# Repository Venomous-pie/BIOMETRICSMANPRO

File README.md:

# Biometrics Time-In/Out System

An ESP32-based biometric attendance system. A fingerprint scanner node (WROOM) communicates wirelessly via ESP-NOW to a touchscreen display node (CrowPanel), which connects to the backend over WiFi.

---

## Table of Contents

1. [Architecture Overview](#1-architecture-overview)
2. [Hardware](#2-hardware)
3. [Power Requirements](#3-power-requirements)
4. [Wiring & Pinout](#4-wiring--pinout)
5. [Arduino IDE Setup](#5-arduino-ide-setup)
6. [Configuration Reference](#6-configuration-reference)
7. [First-Time Flash Order](#7-first-time-flash-order)
8. [Mock Server Usage](#8-mock-server-usage)
9. [Repository Layout](#9-repository-layout)
10. [Employee Sync Pipeline](#10-employee-sync-pipeline)
11. [ESP-NOW Message Types](#11-esp-now-message-types)
12. [Persistent Storage Map](#12-persistent-storage-map)
13. [Subsystem Deep-Dives](#13-subsystem-deep-dives)
14. [Development Workflow](#14-development-workflow)
15. [WROOM Serial Commands](#15-wroom-serial-commands)
16. [Testing Checklist](#16-testing-checklist)
17. [Backend API Endpoints](#17-backend-api-endpoints)
18. [Open Work & Known Issues](#18-open-work--known-issues)
19. [OTA Firmware Update Roadmap](#19-ota-firmware-update-roadmap)
20. [Design Notes](#20-design-notes)

---

## 1. Architecture Overview

Understanding the data flow before touching code will save you hours. The system has three tiers:

```
+-----------------------------------+        +-----------------------------------+
|      WROOM Node (ESP32-D0WD-V3)   |        |   CrowPanel Node (ESP32-S3 QFN56) |
|                                   |        |                                   |
|  AS608 Fingerprint Sensor         |        |  5" 800x480 Touchscreen (LVGL)    |
|  WiFi (NTP timekeeping — RTC TBD) |        |  Employee list and logs UI        |
|  WiFi (for NTP + backend calls)   |        |  WiFi (for backend sync)          |
|                                   |        |                                   |
|  Polls finger -> match -> sends   |<------>|  Receives match/enroll events     |
|  attendance event over ESP-NOW    | ESP-NOW|  Shows result screen              |
|                                   |        |                                   |
|  Handles: activation, NTP sync,   |        |  Handles: employee list sync,     |
|  fingerprint enroll/delete,       |        |  attendance log display,          |
|  factory reset                    |        |  WiFi setup UI, settings          |
+------------------+----------------+        +------------------+----------------+
                   | HTTPS (REST API)                            | HTTPS (REST API)
                   +---------------------------+-----------------+
                                               |
                                    +----------v-----------+
                                    |    ManPro Backend API |
                                    |  (demo.manpromanage- |
                                    |   ment.com or local  |
                                    |   mock server)        |
                                    +----------------------+
```

**How a time-in works, end to end:**

1. Employee places finger on the AS608 sensor on the WROOM.
2. WROOM matches the fingerprint to a stored template and resolves the employee ID.
3. WROOM sends a `{type: MATCH, emp_id: ..., ts: ...}` JSON packet to the CrowPanel via ESP-NOW.
4. CrowPanel displays the result screen (welcome / access denied) and logs the attendance locally.
5. CrowPanel uploads the log entry to the backend API over WiFi on the next sync cycle.

**ESP-NOW channel management:** Both nodes must use the same WiFi channel. The WROOM monitors the channel continuously; if the AP hops channels, the WROOM sends a `CHANNEL_HOP` notification so the CrowPanel resyncs without a reboot.

---

## 2. Hardware

| Node      | Board                        | Chip                 | Role                                     |
| --------- | ---------------------------- | -------------------- | ---------------------------------------- |
| CrowPanel | Elecrow CrowPanel 5" 800×480 | **ESP32-S3 (QFN56)** | Touchscreen UI, WiFi, backend comms      |
| WROOM     | ESP32-WROOM-32 dev module    | **ESP32-D0WD-V3**    | Fingerprint scanner, ESP-NOW bridge      |

### CrowPanel SD Card Requirement (Deep Storage)

The system uses a **Smart Cache** architecture. The WROOM's AS608 fingerprint sensor acts as a fast L1 cache holding 127 active templates. The CrowPanel's SD Card acts as the primary "Deep Storage", holding an unlimited number of fingerprint templates for offline scale.

- **Requirement:** A MicroSD card (FAT32 formatted) must be inserted into the CrowPanel.
- **Directory Structure:** The firmware expects the directory `/templates/` at the root of the SD card.
- **File Format:** Templates are stored as raw 512-byte binary files (e.g., `/templates/<emp_id>_<finger_index>.bin`).

---

## 3. Power Requirements

### Supply Voltages

| Component                        | Voltage                        | Typical Current                                 | Peak Current                      |
| -------------------------------- | ------------------------------ | ----------------------------------------------- | --------------------------------- |
| ESP32-D0WD-V3 (WROOM-32 module)  | 3.3 V                          | ~80 mA idle                                     | ~350 mA WiFi TX burst             |
| CrowPanel ESP32-S3 (QFN56) board | 5 V (USB-C) or 3.3 V regulated | ~150 mA idle                                    | ~500 mA with LCD backlight + WiFi |
| AS608 Fingerprint Sensor         | 3.3 V                          | ~120 mA scanning                                | ~140 mA                           |
| DFPlayer Mini + Speaker          | 5.0 V                          | ~20 mA idle                                     | ~200 mA playing                   |

### Power Strategy

**During development:**

- Power the **CrowPanel** via its USB-C port from a PC or USB charger. The board has an onboard 3.3 V LDO — you do not need a separate regulator.
- Power the **WROOM dev board** via its USB-micro/USB-C port. Most WROOM dev boards also have a 3.3 V LDO.
- The **AS608** can be powered from the WROOM board's 3.3 V pin (labelled `3V3`). Its draw (~120–140 mA) is well within the AMS1117 LDO's 800 mA rating.

**In the final enclosure:**

- The WROOM + AS608 sub-assembly should be powered from a regulated **5 V 1 A** supply (e.g. USB wall adapter) feeding the WROOM dev board's USB connector, or via VIN if using a bare module with an external 3.3 V regulator.
- The CrowPanel should be powered independently via its USB-C connector from a **5 V 2 A** source. Its LCD backlight alone draws ~200 mA.
- **Do not share a USB port between the two boards** during development — each board needs its own Serial port for log monitoring and flashing.

### Wire Gauge

- For power rails: 26 AWG stranded is sufficient for the current levels involved.
- For UART signal lines: 28 AWG or 30 AWG.
- Keep wire runs under 30 cm to avoid voltage drop on the 3.3 V rail.

---

## 4. Wiring & Pinout

### WROOM — Complete Pin Map

| Pin          | GPIO          | Function                   | Notes                                           |
| ------------ | ------------- | -------------------------- | ----------------------------------------------- |
| 3V3          | —             | 3.3 V output               | Powers AS608                              |
| GND          | —             | Ground                     | Common ground for all peripherals         |
| **UART1 RX** | **GPIO27**    | AS608 TX ->                | Connect to AS608 TXD pin                  |
| **UART1 TX** | **GPIO26**    | AS608 RX <-                | Connect to AS608 RXD pin                  |
| **GPIO34**   | Input-only    | AS608 T-OUT (touch detect) | Pulled HIGH by sensor when finger present |
| **GPIO21**   | SDA           | Reserved — RTC (future)    | Not connected; reserved for DS3231 I2C    |
| **GPIO22**   | SCL           | Reserved — RTC (future)    | Not connected; reserved for DS3231 I2C    |
| **UART2 RX** | **GPIO17**    | DFPlayer TX <-             | Audio RX (Use Logic Level Shifter!)             |
| **UART2 TX** | **GPIO16**    | DFPlayer RX ->             | Audio TX (Use Logic Level Shifter!)             |
| **GPIO13**   | Output        | Reserved — Buzzer (future) | Not connected; reserved for buzzer signal       |
| **GPIO14**   | Factory Reset | Active HIGH button         | Uses internal pull-down; hold 5 s to wipe       |

**Pins to avoid on ESP32-D0WD-V3 (WROOM-32):**

| GPIO      | Reason                                                                              |
| --------- | ----------------------------------------------------------------------------------- |
| GPIO0     | Strapping pin — LOW at boot = download mode; do not pull low with external hardware |
| GPIO2     | Strapping pin — must be LOW during flash; avoid driving it during boot              |
| GPIO12    | Strapping pin — sets flash voltage; keep floating or LOW                            |
| GPIO15    | Strapping pin — controls boot logging; keep floating for normal use                 |
| GPIO34–39 | Input-only — no internal pull-up/pull-down; cannot be driven as outputs             |
| GPIO6–11  | Connected to internal SPI flash — do not use                                        |

**Connector type:** JST-PH 2.0 mm 2-pin or standard 2.54 mm DuPont headers are both fine for a prototype enclosure.

---

### AS608 Fingerprint Sensor Wiring

| AS608 Pin | Connects to                  |
| --------- | ---------------------------- |
| VCC       | WROOM 3V3                    |
| GND       | WROOM GND                    |
| TXD       | WROOM GPIO27 (UART1 RX)      |
| RXD       | WROOM GPIO26 (UART1 TX)      |
| T-OUT     | WROOM GPIO34                 |
| WAKEUP    | Leave floating or tie to GND |

> The AS608 communicates at 57600 baud by default. The firmware initialises UART1 at this speed. Do not change it unless you also update `fingerprint_manager.cpp`.

---

### Audio (DFPlayer Mini) Wiring

> **Hardware Setup Notes:**
>
> - **Logic Level Converter:** The ESP32 is a 3.3V device, but the DFPlayer Mini runs best at 5V. The RX/TX lines are routed through a logic level converter to protect the ESP32 pins.
> - **Active Buzzer (Not Implemented — Future Work):** The active buzzer has not been integrated into the hardware. GPIO13 is physically reserved for it. When implemented, it requires an NPN transistor and a flyback diode to drive safely from the ESP32.

| Audio Pin         | Connects to                                             | Notes                                                                       |
| ----------------- | ------------------------------------------------------- | --------------------------------------------------------------------------- |
| DFPlayer VCC      | 5V Power Rail                                           | Provide 5V for loud/clean audio                                             |
| DFPlayer GND      | Common GND                                              |                                                                             |
| DFPlayer RX       | Logic Level Converter (HV) -> (LV) -> WROOM GPIO16 (TX) | Converts 3.3V TX to 5V                                                      |
| DFPlayer TX       | Logic Level Converter (HV) -> (LV) -> WROOM GPIO17 (RX) | Converts 5V TX to 3.3V                                                      |
| DFPlayer SPK+     | Speaker Positive (+)                                    |                                                                             |
| DFPlayer SPK-     | Speaker Negative (-)                                    |                                                                             |

_Place your audio files (e.g., `0001.mp3`, `0002.mp3`) inside a folder literally named `mp3` on the root of the SD card before inserting it into the DFPlayer._

---

### DS3231 RTC Module (Not Implemented — Future Work)

> **The DS3231 hardware RTC has not been integrated into the firmware.** GPIO21 (SDA) and GPIO22 (SCL) are physically reserved for it, and the `time_manager.cpp` file exists as a stub, but the RTC driver is not initialised at boot. The WROOM currently uses NTP as its sole time source and falls back to `millis()`-based offset if WiFi is unavailable.
>
> Integrating the DS3231 is tracked as a future implementation item. When implemented, refer to the wiring table below:

| DS3231 Pin | Planned Connection |
| ---------- | ------------------ |
| VCC        | WROOM 3V3          |
| GND        | WROOM GND          |
| SDA        | WROOM GPIO21       |
| SCL        | WROOM GPIO22       |
| SQW        | Not connected      |
| 32K        | Not connected      |

---

### CrowPanel — Key Pins

The CrowPanel 5" board is a self-contained unit. You do not need to wire any peripherals to it — the display, touch controller, and SD card are all onboard. The only external connection is USB-C for power and flashing.

| Function      | Notes                                                |
| ------------- | ---------------------------------------------------- |
| USB-C         | Power + Serial (CDC) for flashing and Serial Monitor |
| ESP-NOW radio | Uses onboard antenna; no external connection needed  |
| WiFi          | Uses onboard antenna                                 |

**Pins to avoid on ESP32-S3 (QFN56) (if you ever need to expand):**

| GPIO           | Reason                                  |
| -------------- | --------------------------------------- |
| GPIO0          | Strapping pin — boot mode selection     |
| GPIO3          | Strapping pin                           |
| GPIO19, GPIO20 | USB D+/D− — used by CDC USB port        |
| GPIO26–32      | Connected to OPI PSRAM — do not use     |
| GPIO33–37      | Connected to onboard flash — do not use |

---

## 5. Arduino IDE Setup

**Version:** Arduino IDE 2.3.10

> Since the IDE's Tools menu settings are **per-board-selection** and do not persist per-sketch, always double-check the **Board** dropdown before flashing. Flashing the wrong sketch to the wrong board (or with the wrong partition scheme) will produce a silent bad build.

### Step 1 — Install Arduino IDE

Download the installer from https://www.arduino.cc/en/software — choose **Arduino IDE 2.3.10** (Windows Installer). Run with default options.

### Step 2 — Add the ESP32 Board Package

1. Open Arduino IDE -> **File -> Preferences**.
2. In **Additional boards manager URLs**, paste:
   ```
   https://raw.githubusercontent.com/espressif/arduino-esp32/gh-pages/package_esp32_index.json
   ```
3. Click **OK**.
4. Go to **Tools -> Board -> Boards Manager**, search for `esp32`, and install **esp32 by Espressif Systems**.
   - **Required version: 3.2.0** (or the latest 3.x release). Version 2.x is not compatible with the ESP32-S3 PSRAM driver used by the CrowPanel.

### Step 3 — Install Libraries

Open **Tools -> Manage Libraries** and install each of the following by searching the Library Manager:

**For CrowPanel:**

| Search Term      | Library to Install      | Pin Version To |
| ---------------- | ----------------------- | -------------- |
| Adafruit BusIO   | Adafruit BusIO          | 1.17.4         |
| DFRobot DFPlayer | DFRobotDFPlayerMini     | 1.0.6          |
| LovyanGFX        | LovyanGFX (by lovyan03) | 1.2.25         |
| lvgl             | lvgl (by kisvegabor)    | **8.3.11**     |

> ⚠️ **LVGL is pinned to 8.3.11.** Version 9.x contains breaking API changes affecting `lv_obj_t` styling and display driver registration. Do **not** allow Library Manager to auto-update this library.

**For WROOM:**

| Search Term          | Library to Install                  | Version |
| -------------------- | ----------------------------------- | ------- |
| Adafruit BusIO       | Adafruit BusIO                      | 1.17.4  |
| Adafruit Fingerprint | Adafruit Fingerprint Sensor Library | 2.1.4   |
| ArduinoJson          | ArduinoJson (by Benoit Blanchon)    | 7.4.3   |

The following are used directly but bundled with the ESP32 board package — no separate install needed: `WiFi`, `WiFiUdp`, `HTTPClient`, `esp_now`, `esp_system`, `esp_wifi`, `Preferences`, `Wire`, `time.h`.

---

### CrowPanel — ESP32-S3 (QFN56) Board Settings

| Setting                              | Value                                |
| ------------------------------------ | ------------------------------------ |
| Board                                | ESP32S3 Dev Module                   |
| USB CDC On Boot                      | Enabled                              |
| CPU Frequency                        | 240MHz (WiFi)                        |
| Core Debug Level                     | None                                 |
| USB DFU On Boot                      | Disabled                             |
| Erase All Flash Before Sketch Upload | Disabled                             |
| Events Run On                        | Core 1                               |
| Flash Mode                           | QIO 80MHz                            |
| Flash Size                           | 4MB (32Mb)                           |
| JTAG Adapter                         | Disabled                             |
| Arduino Runs On                      | Core 1                               |
| USB Firmware MSC On Boot             | Disabled                             |
| **Partition Scheme**                 | **Huge APP (3MB No OTA/1MB SPIFFS)** |
| **PSRAM**                            | **OPI PSRAM**                        |
| Upload Mode                          | UART0 / Hardware CDC                 |
| Upload Speed                         | 921600                               |
| USB Mode                             | Hardware CDC and JTAG                |
| Zigbee Mode                          | Disabled                             |

### WROOM Controller — ESP32-D0WD-V3 Board Settings

| Setting                                  | Value                                                |
| ---------------------------------------- | ---------------------------------------------------- |
| Board                                    | ESP32 Dev Module                                     |
| CPU Frequency                            | 240MHz (WiFi/BT)                                     |
| Core Debug Level                         | None                                                 |
| **Erase All Flash Before Sketch Upload** | **Enabled**                                          |
| Events Run On                            | Core 1                                               |
| Flash Frequency                          | 80MHz                                                |
| Flash Mode                               | QIO                                                  |
| Flash Size                               | 4MB (32Mb)                                           |
| JTAG Adapter                             | Disabled                                             |
| Arduino Runs On                          | Core 1                                               |
| **Partition Scheme**                     | **Default 4MB with spiffs (1.2MB APP/1.5MB SPIFFS)** |
| **PSRAM**                                | **Disabled**                                         |
| Upload Speed                             | 921600                                               |
| Zigbee Mode                              | Disabled                                             |

> **WROOM:** "Erase All Flash Before Sketch Upload" must be Enabled. The Preferences (NVS) partition layout changed during development and stale data causes silent failures on boot.

---

## 6. Configuration Reference

All runtime-tunable values are defined in the files below. Edit these before flashing to match your environment.

### `wroom_firmware/src/config.h`

| Constant             | Default                             | What it controls                                                                                                  |
| -------------------- | ----------------------------------- | ----------------------------------------------------------------------------------------------------------------- |
| `DEVICE_ID`          | `F001-2608-6AEC-ON92`               | Unique device identifier sent to backend during activation. Must match `DEVICE_ID_HARDCODED` in `data_manager.h`. |
| `API_BASE_URL`       | `https://demo.manpromanagement.com` | Backend base URL. Change to `http://192.168.x.x:8000` for local mock server.                                      |
| `ESPNOW_CHANNEL`     | `1`                                 | Fixed WiFi channel for ESP-NOW. Your router must be locked to this channel.                                       |
| `ESPNOW_PAYLOAD_MAX` | `251`                               | Maximum ESP-NOW packet size in bytes. Do not increase beyond 250.                                                 |
| `PIN_FP_RX`          | `27`                                | UART1 RX — receives data from AS608 TXD pin.                                                                      |
| `PIN_FP_TX`          | `26`                                | UART1 TX — sends data to AS608 RXD pin.                                                                           |
| `PIN_FP_TOUCH`       | `34`                                | Input from AS608 T-OUT (finger present detect).                                                                   |
| `PIN_FACTORY_RESET`  | `14`                                | Active-HIGH button. Hold for 5 s to factory reset.                                                                |
| `MAX_SLOTS`          | `127`                               | AS608 fingerprint template slot limit. Do not increase.                                                           |

### `wroom_firmware/src/comms.cpp`

| Variable           | Default             | What it controls                                                                                          |
| ------------------ | ------------------- | --------------------------------------------------------------------------------------------------------- |
| `CROWPANEL_MAC[6]` | `{0x30, 0xED, ...}` | Station MAC address of the CrowPanel. **You must update this** before flashing the WROOM (see Section 7). |

### `crowpanel_firmware/src/core/comm_manager.h`

| Variable       | Default                             | What it controls                                                                          |
| -------------- | ----------------------------------- | ----------------------------------------------------------------------------------------- |
| `WROOM_MAC[6]` | `{0x30, 0x76, ...}`                 | Station MAC address of the WROOM. **You must update this** before flashing the CrowPanel. |
| `API_BASE_URL` | `https://demo.manpromanagement.com` | Backend base URL for CrowPanel attendance uploads.                                        |

### `crowpanel_firmware/src/core/data_manager.h`

| Constant              | Default               | What it controls                                                                                                                   |
| --------------------- | --------------------- | ---------------------------------------------------------------------------------------------------------------------------------- |
| `DEVICE_ID_HARDCODED` | `F001-2608-6AEC-ON92` | Must match `DEVICE_ID` in WROOM `config.h`. Both boards send this to the backend to prove they belong to the same registered unit. |

> ⚠️ **The device ID versioning scheme is not yet defined.** `data_manager.h` has a TODO: _"Make this dynamic, get the versioning pattern from senior dev."_ For now, assign IDs manually and keep them in sync across both files.

### Time / NTP (`wroom_firmware/src/time_manager.cpp`)

> **Note:** The DS3231 RTC is not yet implemented. `time_manager.cpp` currently only handles NTP sync and `millis()`-based fallback.

| Value               | Default                  | What it controls                                                           |
| ------------------- | ------------------------ | -------------------------------------------------------------------------- |
| UTC offset          | `8 * 3600` (UTC+8 / PST) | Change the multiplier for your timezone, e.g. `7 * 3600` for ICT (UTC+7). |
| Primary NTP server  | `pool.ntp.org`           | Standard global NTP pool.                                                  |
| Fallback NTP server | `time.google.com`        | Used if the primary is unreachable.                                        |

### WiFi Credentials

WiFi credentials are **not** hardcoded — they are entered at runtime via the CrowPanel **Settings -> WiFi** screen and stored in LittleFS. There is no file to edit for WiFi; just use the on-device UI.

---

## 7. First-Time Flash Order

> Always flash the CrowPanel first. The WROOM needs the CrowPanel's MAC address baked in before it can pair.

### Step 1 — Flash CrowPanel and get its MAC

1. Open `crowpanel_firmware/crowpanel_firmware.ino` in Arduino IDE.
2. Select **Tools -> Board -> ESP32S3 Dev Module** and apply all settings from the CrowPanel board settings table.
3. Connect the CrowPanel via USB-C. Select its port under **Tools -> Port**.
4. Click **Upload** (arrow button). Wait for "Done uploading."
5. Open **Tools -> Serial Monitor**. Set baud rate to **115200** and line ending to **Newline**.
6. Press the reset button on the CrowPanel (or power-cycle it).
7. Wait for the boot log. Within ~3 seconds you should see:
   ```
   [BOOT] CP MAC: 30:ED:A0:31:70:EC
   [DISPLAY] Init OK
   [LVGL] Ready
   ```
8. **Copy the full MAC address** from the `[BOOT] CP MAC:` line.

> **If nothing appears in Serial Monitor:** Make sure `USB CDC On Boot` is set to **Enabled** in board settings, and that you have selected the correct COM port. On Windows, open Device Manager and look for "USB Serial Device (COMx)" under Ports.

---

### Step 2 — Update WROOM firmware with CrowPanel MAC

1. Open `wroom_firmware/src/comms.cpp`.
2. Find the line:
   ```cpp
   uint8_t CROWPANEL_MAC[6] = {0x30, 0xED, 0xA0, 0x31, 0x70, 0xEC};
   ```
3. Replace the 6 hex bytes with the MAC you copied in Step 1. For example, if the MAC was `A4:CF:12:AB:CD:EF`:
   ```cpp
   uint8_t CROWPANEL_MAC[6] = {0xA4, 0xCF, 0x12, 0xAB, 0xCD, 0xEF};
   ```
4. Also update `WROOM_MAC[6]` in `crowpanel_firmware/src/core/comm_manager.h` with the WROOM's own MAC (shown as `[BOOT] WROOM MAC:` when you flash the WROOM in Step 3).
5. Save both files.

---

### Step 3 — Flash WROOM

1. Open `wroom_firmware/wroom_firmware.ino` in Arduino IDE.
2. Select **Tools -> Board -> ESP32 Dev Module** and apply all settings from the WROOM board settings table.
3. Connect the WROOM via USB. Select its port under **Tools -> Port**.
4. Click **Upload**. Because `Erase All Flash Before Sketch Upload` is enabled, this takes ~30 seconds on the first flash.
5. Open **Tools -> Serial Monitor** at **115200 baud**.
6. Press reset on the WROOM. Expected boot sequence:
   ```
   === Biometrics WROOM Controller ===
   [BOOT] Reset reason: 1
   [WIFI] Attempting to connect to saved network...
   [AS608] Found! Templates stored: 3
   [ESPNOW] Peer registered: 30:ed:a0:31:70:ec
   Ready. Serial commands:
     ENROLL:<emp_id>:<finger_index>  e.g. ENROLL:1:0
     DELETE:<emp_id>:<finger_index>  e.g. DELETE:1:0
     RESET
   ```
7. Note the `[BOOT] WROOM MAC:` line. Go back and update `WROOM_MAC[6]` in `comm_manager.h` if not already done, then re-flash the CrowPanel.
8. On the CrowPanel, you should briefly see a "WROOM online" toast confirming the link is live.

---

### Step 4 — WiFi Setup and Activation

1. On the CrowPanel, navigate to **Settings -> WiFi**.
2. Scan for networks, select your AP, and enter the password using the on-screen keyboard.
3. Once connected, navigate to **Settings -> Activation** and enter your ManPro registration code.
4. The WROOM calls the backend API to validate, and both boards mark themselves as activated.

---

### Pairing Troubleshooting

| Symptom                                        | Likely Cause                     | Fix                                                                      |
| ---------------------------------------------- | -------------------------------- | ------------------------------------------------------------------------ |
| `[ESPNOW] Send fail` repeated in WROOM Serial  | Wrong MAC address in `comms.cpp` | Re-read CrowPanel MAC and update `comms.cpp`.                            |
| No "WROOM online" toast on CrowPanel           | Channel mismatch                 | Lock router to a fixed channel and match `ESPNOW_CHANNEL` in `config.h`. |
| `[AS608] NOT FOUND` in WROOM Serial            | Wiring error or wrong baud       | Check GPIO26/27 connections. Swap RX/TX if reversed.                     |

| CrowPanel shows blank/white screen after flash | Wrong partition or PSRAM setting | Re-check: Partition = Huge APP, PSRAM = OPI PSRAM.                       |

---

## 8. Mock Server Usage

Use the mock server during development when you do not have access to the live ManPro backend.

### Prerequisites

- Python 3.9 or later
- `pip install flask`

### Starting the Mock Server

```bash
cd mock_server
pip install -r requirements.txt
python mock_server.py
```

The server starts on `http://0.0.0.0:8000` by default and prints available endpoints on startup.

### Pointing the Firmware at the Mock Server

1. Find your development machine's LAN IP address (e.g. `192.168.1.50`).
2. Open `wroom_firmware/src/config.h` and change:
   ```cpp
   #define API_BASE_URL "http://192.168.1.50:8000"
   ```
3. Also change `API_BASE_URL` in `crowpanel_firmware/src/core/comm_manager.h` to the same value.
4. Ensure both devices and your development machine are on the same WiFi network, then flash.

> The mock server returns canned responses for all endpoints. Check its console output to see every request the firmware makes — this is useful for debugging sync issues.

> `crowpanel_firmware/tools/admin_mock.py` is a separate, lightweight admin mock. It is **incomplete** and does not cover all endpoints — use the main mock server above instead.

---

## 9. Repository Layout

```
BIOMETRICSMANPRO/
├── README.md                             # This file
├── docs/
│   └── admin_manual.md                  # End-user / admin UI guide
├── crowpanel_firmware/
│   ├── crowpanel_firmware.ino            # Entry point: setup() + loop(), LVGL init
│   ├── tools/
│   │   ├── convert_img.py               # Converts PNG -> LVGL C array
│   │   ├── run_conv.py                  # Batch runner for convert_img.py
│   │   └── admin_mock.py               # Partial admin API mock (incomplete)
│   └── src/
│       ├── core/
│       │   ├── display_driver.h         # LovyanGFX LGFX config (pins, resolution, touch)
│       │   ├── data_manager.h/.cpp      # All persistent state: employees, logs, settings
│       │   ├── comm_manager.h/.cpp      # ESP-NOW init, RX ring buffer, JSON dispatch
│       │   ├── sync_receiver.h/.cpp     # Binary protocol handler for employee sync
│       │   ├── sync_protocol.h          # Shared packet structs (MUST match WROOM copy)
│       │   └── certs.h                  # GTS Root R4 CA cert for HTTPS
│       ├── ui/
│       │   ├── ui_manager.h/.cpp        # Screen router, showXxx() navigation
│       │   ├── ui_idle.h/.cpp           # Standby screen (clock, finger prompt)
│       │   ├── ui_result.h/.cpp         # Post-scan feedback (green=OK, red=fail)
│       │   ├── ui_pin.h/.cpp            # Admin PIN entry + lockout logic
│       │   ├── ui_main_menu.h/.cpp      # Admin hub (Enroll / Logs / Settings)
│       │   ├── ui_enroll.h/.cpp         # Fingerprint enrolment wizard
│       │   ├── ui_logs.h/.cpp           # Attendance log viewer
│       │   ├── ui_settings.h/.cpp       # Settings hub
│       │   ├── ui_settings_clock.h/.cpp # Manual time/date picker
│       │   ├── ui_settings_danger.h/.cpp# Factory reset / nuke confirmations
│       │   ├── ui_settings_display.h/.cpp # Brightness + timeout sliders
│       │   ├── ui_settings_server.h/.cpp# API base URL override
│       │   ├── ui_wifi_setup.h/.cpp     # WiFi scan + connect UI
│       │   ├── ui_sync_status.h/.cpp    # Sync log viewer
│       │   └── ui_activation.h/.cpp     # Device registration screen
│       ├── splash/
│       │   └── manpro_splash.h          # Boot animation (calls UIManager::loadInitialScreen)
│       └── assets/                      # Compiled LVGL C arrays (icons, fonts)
├── wroom_firmware/
│   ├── wroom_firmware.ino               # Entry point: setup() + loop()
│   └── src/
│       ├── config.h                     # Pin defs, DEVICE_ID, API_BASE_URL, ESP-NOW constants
│       ├── certs.h                      # GTS Root R4 CA cert for HTTPS
│       ├── employee_db.h/.cpp           # Slot->emp_id mapping (stored in NVS)
│       ├── comms.h/.cpp                 # ESP-NOW send/recv, ring buffer, CROWPANEL_MAC
│       ├── wifi_manager.h/.cpp          # WiFi connect, scan, auto-reconnect
│       ├── time_manager.h/.cpp          # NTP timekeeping + millis fallback (DS3231 RTC: future work)
│       ├── fingerprint_manager.h/.cpp   # AS608 sensor: match, enroll, delete
│       ├── activation.h/.cpp            # POST /api/devices/activate -> store token
│       ├── sync_manager.h/.cpp          # Employee sync state machine
│       ├── sync_protocol.h             # Shared packet structs (MUST match CrowPanel copy)
│       └── command_handler.h/.cpp       # Dispatches Serial + ESP-NOW JSON commands
├── assets/
│   ├── logo/                            # Source ManPro logo PNGs
│   ├── icons/                           # Source icon PNGs (converted by tools/)
│   └── boot_anim/                       # Boot animation frames
└── ui_reference/                        # Color palette & design reference screenshots
```

---

## 10. Employee Sync Pipeline

The employee list lives on the ManPro backend. This is the most complex subsystem.

```
ManPro Backend API
     |
     |  GET /api/devices/employees  (HTTPS, Bearer token)
     v
WROOM: SyncManager::fetchEmployeesFromApi()
     |  Parses JSON -> EmployeeSync[] buffer
     |  Handles 5 wrapper key styles: "employees", "data", "result", "payload", bare array
     |
     |  Binary framed over ESP-NOW (sync_protocol.h)
     |  PING -> PONG -> SYNC_START -> SYNC_DATA[n] -> SYNC_END -> SYNC_RESULT
     v
CrowPanel: SyncReceiver
     |  Assembles chunks, verifies CRC32
     |  DataManager::applySyncBuffer() -> empDB[]
     |  Persists to LittleFS (/employees.json)
     |  DataManager::loadFpState() re-applies enrollment bitmask after overwrite
     v
     SYNC_RESULT (OK or NACK with list of missing chunk indices)
     v
WROOM: SyncManager::handleIncomingPacket()
     |  OK  -> SYNC_STATE_IDLE
     |  NACK -> resend missing chunks -> re-send SYNC_END
```

### SyncManager State Machine (WROOM)

States in order:
`IDLE -> FETCH_WIFI -> SET_ESPNOW_CHANNEL -> SEND_PING -> SEND_SYNC_START -> SEND_CHUNKS -> SEND_SYNC_END -> AWAIT_SYNC_RESULT`

- Failure at any state triggers `failToFastRetry()` — enters `FAST_RETRY_MODE` (retries every 5 minutes).
- Sync triggers: (a) manually via `SYNC_EMP` ESP-NOW command from CrowPanel, or (b) automatically at the top of every hour when NTP time is valid.
- **BUG-10 fix** (applied): `s_syncEndResendCount` is a separate counter from `s_retryCount` because `setState()` resets `s_retryCount` — a unified counter made the 3-retry limit on SYNC_END resends unreachable.
- **EDGE-07 fix** (applied): `sync_id` falls back to a monotonic counter if `time(NULL)` returns a pre-NTP epoch value (< 1,000,000,000), preventing stale-packet acceptance from a prior session.

### sync_protocol.h — The Contract

Both firmwares include a **copy** of `sync_protocol.h`. They must be **byte-for-byte identical**. If you change a struct or add a packet type, update both copies. Struct sizes are enforced at compile time via `static_assert`.

| Packet                    | Direction           | Purpose                                       |
| ------------------------- | ------------------- | --------------------------------------------- |
| `SYNC_PING` / `SYNC_PONG` | WROOM <-> CrowPanel | Confirm ESP-NOW link before starting          |
| `SYNC_START`              | WROOM -> CrowPanel  | Declares `sync_id`, total chunks, total bytes |
| `SYNC_DATA`               | WROOM -> CrowPanel  | One chunk of raw `EmployeeSync[]` bytes       |
| `SYNC_CHUNK_ACK`          | CrowPanel -> WROOM  | Confirms receipt of a specific chunk index    |
| `SYNC_END`                | WROOM -> CrowPanel  | Signals completion, carries CRC32             |
| `SYNC_RESULT`             | CrowPanel -> WROOM  | OK or NACK with list of missing chunk indices |

`MAX_SYNC_EMPLOYEES = 127` — matches the AS608 slot limit. Do not increase without also expanding the fingerprint slot pool.  
`MAX_CHUNK_SIZE = 200` bytes — the largest transmitted packet must stay ≤ 250 bytes (ESP-NOW hard limit).

---

## 11. ESP-NOW Message Types

Most inter-node communication uses **JSON strings** sent over ESP-NOW. Only the employee sync uses binary packets (see Section 10). The message type field is `"type"`. The CrowPanel's `CommManager::dispatchJson()` routes all incoming JSON messages.

| `type`              | Direction          | Description                                                              |
| ------------------- | ------------------ | ------------------------------------------------------------------------ |
| `MATCH`             | WROOM -> CrowPanel | Fingerprint matched: `{emp_id, name, ts, confidence, slot, action_type}` |
| `ENROLL_RESULT`     | WROOM -> CrowPanel | Enrolment result: `{success, emp_id, finger_index, slot, msg}`           |
| `EMP_SYNC_START`    | CrowPanel -> WROOM | Trigger employee sync (WROOM starts SyncManager)                         |
| `EMP_SYNC_FAIL`     | WROOM -> CrowPanel | Sync failed — stop UI loading spinner                                    |
| `ACTIVATION_STATUS` | WROOM -> CrowPanel | Activation API result: `{activated, token}`                              |
| `NTP_STATUS`        | WROOM -> CrowPanel | Timestamp string to set CrowPanel RTC: `{time_str}`                      |
| `WIFI_STATUS`       | WROOM -> CrowPanel | WiFi state update: `{connected, ssid, ip}`                               |
| `CHANNEL_HOP`       | WROOM -> CrowPanel | AP changed channel; CrowPanel must re-init ESP-NOW                       |
| `WROOM_ONLINE`      | WROOM -> CrowPanel | Heartbeat on boot — triggers "WROOM online" toast                        |
| `GHOST_LOGIN`       | WROOM -> CrowPanel | Dev backdoor — bypasses scanner, opens Main Menu                         |
| `NUKE_USERS`        | WROOM -> CrowPanel | Dev backdoor — erases all fingerprint slots except slot 1                |
| `DEBUG_COMMS`       | WROOM -> CrowPanel | Dev backdoor — toggles ESP-NOW ping/pong debug output                    |

---

## 12. Persistent Storage Map

### WROOM — NVS (Preferences namespace `"biometrics"`)

| Key            | Type   | Content                           |
| -------------- | ------ | --------------------------------- |
| `activated`    | bool   | Whether device has been activated |
| `device_token` | String | Bearer token from backend         |
| `wifi_ssid`    | String | Saved WiFi network                |
| `wifi_pass`    | String | Saved WiFi password               |
| `emp_count`    | int    | Number of entries in slot map     |
| `emp_X_id`     | String | Employee ID for slot X            |
| `emp_X_fi`     | int    | Finger index for slot X           |

The AS608 sensor is the physical store for fingerprint templates. NVS only stores the slot→emp_id lookup table, managed by `employee_db.h/.cpp`.

### CrowPanel — LittleFS

| File               | Format                 | Content                                                                               |
| ------------------ | ---------------------- | ------------------------------------------------------------------------------------- |
| `/employees.json`  | JSON array             | Employee list (name, dept, job_title, branch, fp_enrolled, enrolled_fingers)          |
| `/config.json`     | JSON object            | Device settings (brightness, timeout, volume, adminPin, deviceName, activated, token) |
| `/wifi.json`       | JSON array (up to 5)   | Saved WiFi credentials                                                                |
| `/attendance.json` | JSON array (up to 200) | Local attendance log (name, time_str, action_type, synced, confidence, slot)          |
| `/fp_state.json`   | JSON object            | Enrollment bitmask per emp_id — persisted separately so it survives sync overwrites   |
| `/sync_log.jsonl`  | JSON Lines             | Last 5 sync event messages with timestamps                                            |

### CrowPanel — SD Card (`/templates/`)

Raw 512-byte binary fingerprint templates stored as `/templates/<emp_id>_<finger_index>.bin`. This is the **Deep Storage** layer — the WROOM's AS608 is L1 cache (127 slots); the SD card is the primary store for larger employee sets. Templates are loaded from SD and pushed to WROOM on demand during enrolment or sync.

---

## 13. Subsystem Deep-Dives

### CrowPanel Boot Sequence

```
setup():
  DataManager::begin()         -> mounts LittleFS, loads all JSON files
  CommManager::begin()         -> inits ESP-NOW, registers onEspNowRecv callback
  lcd.init()                   -> LovyanGFX + GPIO2 backlight reset
  lv_init()                    -> allocates PSRAM render buffers (2x 800x240 px)
  manpro_show_splash(callback) -> plays boot animation, then calls UIManager::loadInitialScreen
  UIManager::begin()           -> builds all LVGL screen objects

loop():
  lv_tick_inc() + lv_task_handler()   -> LVGL rendering tick
  CommManager::process()              -> drains ring buffer, dispatches JSON messages
  Screen timeout check                -> dims backlight after inactivity
```

`UIManager::loadInitialScreen` decides which screen shows after the splash: Activation screen (not activated) → WiFi setup (no saved credentials) → Idle screen (normal operation).

### WROOM Boot Sequence

```
setup():
  WiFiManager::begin()         -> attempts to connect to saved network
  FingerprintManager::init()   -> opens AS608 on UART1, counts stored templates
  TimeManager::init()          -> syncs NTP if WiFi available (DS3231 RTC: not yet implemented)
  Comms::begin()               -> inits ESP-NOW, registers CROWPANEL_MAC as peer
  SyncManager::init()          -> sets state to IDLE
  AudioManager::init()         -> inits DFPlayer Mini on UART2

loop():
  CommandHandler::poll()       -> polls AS608 T-OUT pin, reads Serial commands
  SyncManager::loop()          -> drives sync state machine, hourly auto-trigger
```

### Admin PIN System

- Default PIN: `0000` (set in `DataManager` default config).
- PIN is stored in `/config.json` (plaintext — no hashing currently).
- Lockout: 5 consecutive wrong attempts → 60-second lockout. Tracked in `DataManager::_failedAttempts` / `_lockoutStartTime`, persisted in config across reboots.
- PIN change: **Settings → Danger Zone** (requires current PIN first).
- Admin fingerprint: A special enrolment with `emp_id = "ADMIN"` stored on the SD card. Placing the admin finger on the idle screen opens Main Menu directly without PIN entry.

### Smart Cache Architecture

```
AS608 (WROOM) — L1 cache, 127 slots
  ^ push on enrolment
  v evict: NOT YET IMPLEMENTED (see Section 18)

SD Card (CrowPanel) — Deep storage, unlimited
  /templates/<emp_id>_<finger_index>.bin

ManPro Backend — Source of truth for employee records
```

**Enrolment flow:**

1. CrowPanel UI sends `ENROLL:<emp_id>:<finger_index>` command to WROOM.
2. WROOM captures template on AS608 (gets a physical slot number).
3. WROOM sends the 512-byte template back to CrowPanel in `ENROLL_RESULT`.
4. CrowPanel saves template to SD card.
5. `employee_db` on WROOM stores the slot→emp_id mapping in NVS.

### Time Source Priority

The WROOM currently uses a two-tier clock source:

1. **NTP** (requires WiFi) — synced on boot whenever WiFi is available.
2. **`millis()`-based offset** (last resort — drifts; no persistent timekeeping without WiFi).

> **DS3231 hardware RTC is a planned future implementation.** When added it will serve as a battery-backed middle tier, preserving time across power cycles even without WiFi. GPIO21/22 are already reserved. See the [DS3231 wiring section](#ds3231-rtc-module-not-implemented--future-work) for planned connection details.

---

## 14. Development Workflow

### Sensor-less Testing (WROOM)

Uncomment `#define MOCK_SENSOR 1` in `wroom_firmware/src/config.h`. This simulates fingerprint scans without physical hardware. The `GHOST_LOGIN` Serial command also bypasses the scanner and sends a fake match event to the CrowPanel.

### Image Asset Pipeline

Icons live as source PNGs in `assets/icons/`. To update or add icons:

```bash
cd crowpanel_firmware/tools
python run_conv.py    # batch converts assets/icons/ -> src/assets/*.c
```

The resulting `.c` files are `#include`d into the firmware and declared with `LV_IMG_DECLARE()`.

### Key Files by Area

| Area                                       | Primary Files                                       |
| ------------------------------------------ | --------------------------------------------------- |
| All persistence (CrowPanel)                | `data_manager.h` / `data_manager.cpp`               |
| ESP-NOW receive + JSON routing (CrowPanel) | `comm_manager.h` / `comm_manager.cpp`               |
| Employee sync — sender (WROOM)             | `sync_manager.h` / `sync_manager.cpp`               |
| Employee sync — receiver (CrowPanel)       | `sync_receiver.h` / `sync_receiver.cpp`             |
| Binary packet definitions (both nodes)     | `sync_protocol.h` — **keep both copies identical**  |
| Fingerprint hardware (WROOM)               | `fingerprint_manager.h` / `fingerprint_manager.cpp` |
| All UI screens (CrowPanel)                 | `src/ui/ui_*.h` / `src/ui/ui_*.cpp`                 |
| Screen navigation / routing                | `ui_manager.h` / `ui_manager.cpp`                   |
| Hardware config + pins                     | `wroom_firmware/src/config.h`                       |

---

## 15. WROOM Serial Commands

Connect at **115200 baud**.

| Command                          | Description                                                      |
| -------------------------------- | ---------------------------------------------------------------- |
| `ENROLL:<emp_id>:<finger_index>` | Enroll a finger (e.g. `ENROLL:1:0` = employee 1, first finger)   |
| `DELETE:<emp_id>:<finger_index>` | Erase a stored template (e.g. `DELETE:1:0`)                      |
| `RESET`                          | Reboot the WROOM                                                 |
| `TEST_HW`                        | Hardware test (Plays Track 1)                                    |
| `GHOST_LOGIN`                    | Dev backdoor — bypasses scanner, jumps to Main Menu on CrowPanel |
| `NUKE_USERS`                     | Dev backdoor — erases all stored fingerprints except slot 1      |
| `DEBUG_COMMS`                    | Dev backdoor — toggles ESP-NOW ping/pong debug output            |

---

## 16. Testing Checklist

No automated tests exist. Verify the following manually before any release:

- [ ] Cold boot (power off) → splash animation plays → idle screen loads with correct time
- [ ] Fingerprint time-in → result screen shows correct name and "Time In" → log entry appears in Logs screen
- [ ] Fingerprint time-out → "Time Out" result screen
- [ ] Unrecognized finger → "Not Recognized" result → no log entry written
- [ ] Employee sync triggered from Settings → `[SYNC]` log messages in WROOM Serial → CrowPanel Sync Status screen shows updated employee list
- [ ] Admin PIN: correct PIN opens Main Menu; wrong PIN × 5 triggers 60s lockout
- [ ] WiFi disconnected during sync → WROOM enters FAST_RETRY_MODE → retries after 5 minutes
- [ ] Factory reset on CrowPanel → all data wiped → returns to WiFi setup screen
- [ ] Factory reset on WROOM (hold GPIO14 for 5 s) → fingerprints wiped → NVS cleared
- [ ] Channel hop: change router channel → both nodes re-negotiate within ~10 s

---

## 17. Backend API Endpoints

The firmware calls these endpoints. Consult the ManPro backend team for authentication details and any schema changes.

| Method | Endpoint                 | Caller                       | Purpose                                          |
| ------ | ------------------------ | ---------------------------- | ------------------------------------------------ |
| `POST` | `/api/devices/activate`  | WROOM `activation.cpp`       | Register device, receive bearer token            |
| `GET`  | `/api/devices/employees` | WROOM `sync_manager.cpp`     | Fetch employee list for binary sync to CrowPanel |
| `POST` | `/api/attendance`        | CrowPanel `data_manager.cpp` | Upload attendance log entries                    |

Authentication: `Authorization: Bearer <device_token>` header. Token is obtained during activation and stored in WROOM NVS and CrowPanel `/config.json`.

> `sync_manager.cpp` tries five different JSON wrapper keys (`employees`, `data`, `result`, `payload`, bare array) to handle backend response format variations. If the API schema changes, check `SyncManager::fetchEmployeesFromApi()` first.

---

## 18. Open Work & Known Issues

### Issue 1 — Device ID Versioning Scheme (Undefined)

`DEVICE_ID` in `config.h` and `DEVICE_ID_HARDCODED` in `data_manager.h` are hardcoded strings. A TODO comment in `data_manager.h` reads: _"Make this dynamic, get the versioning pattern from senior dev."_ Until the scheme is defined, IDs must be manually assigned and kept in sync across both files for each physical unit.

### Issue 2 — No Fingerprint Eviction Policy

The AS608 has a hard limit of 127 template slots. There is no LRU or frequency-based eviction policy. If more than 127 fingers are enrolled, enrolment will silently fail. This must be addressed before deploying at any site with more than 127 enrolled fingers.

### Issue 3 — sync_protocol.h Dual-Copy Maintenance Risk

Both `wroom_firmware/src/sync_protocol.h` and `crowpanel_firmware/src/core/sync_protocol.h` must stay byte-for-byte identical. There is no automated check enforcing this. **Any edit to either copy must be manually mirrored to the other.**

### Issue 4 — Admin PIN Stored in Plaintext

The admin PIN is stored as a plain string in `/config.json`. Consider hashing before production deployment.

### Issue 5 — Attendance Upload: No Retry Queue

`DataManager::uploadPendingLogs()` runs attendance POSTs on a FreeRTOS background task. If the task fails mid-batch, those logs remain as `synced=false` and are retried on the next upload cycle. This is acceptable for now but should be replaced with a proper retry queue before production.

### Issue 6 — WiFi Channel Lock Dependency

The router **must** be locked to a fixed channel (default: channel 1). If the router uses auto-channel, the WROOM sends a `CHANNEL_HOP` notification, but this path is not fully hardened. Always configure and test with a fixed channel.

### Issue 7 — OTA Firmware Updates Not Implemented

See Section 19 below.

---

## 19. OTA Firmware Update Roadmap

Both the WROOM and CrowPanel will autonomously check for new firmware over the internet, download it, and apply it — no USB cable needed after the one migration flash.

### How It Will Work

```
Your PC                  GitHub Releases                Devices (anywhere)
------                   ---------------                ------------------
Build .bin files  -push-> firmware_manifest.json        WROOM & CrowPanel
Tag a release           + wroom_v1.1.0.bin              check manifest on boot
                        + crowpanel_v1.1.0.bin  <------  and every 6 hours
                                                               |
                                                    If version newer: download
                                                    .bin over HTTPS -> flash
                                                    -> reboot into new firmware
```

### Open Questions Before Implementation

> ⚠️ **CrowPanel flash size** — The CrowPanel currently uses `Huge APP (3MB No OTA)`, occupying a 3 MB app slot. OTA requires two equal app slots. On a 4 MB chip, two 3 MB slots don't fit. Options:
>
> - **Option A (Recommended):** If the board ships with **16 MB flash** (many do — the `4MB` Arduino setting is a conservative default), use a custom 16 MB partition with two 6 MB app slots.
> - **Option B:** If truly 4 MB flash, reduce the CrowPanel firmware footprint to fit two ~1.9 MB OTA slots (may require stripping some compiled icon assets).
>
> **Action required:** In Arduino IDE with CrowPanel selected, go to `Sketch → Export Compiled Binary` and report the `.bin` file size. If under ~1.7 MB, 4 MB OTA works.

> ⚠️ **One final USB flash required.** Switching partition schemes wipes the existing partition table. Both boards need one last USB flash to migrate to the OTA-capable partition.

### Proposed Changes

**WROOM:**

- `config.h` — add `FIRMWARE_VERSION`, `OTA_MANIFEST_URL`, `OTA_CHECK_INTERVAL_MS`
- New `ota_manager.h/.cpp` — state machine: `IDLE → CHECK_VERSION → DOWNLOADING → DONE/FAILED`; uses `HTTPUpdate` + `GTS_ROOT_R4` cert; sends `OTA_STATUS` JSON to CrowPanel during download
- `command_handler.cpp` — handle `OTA_CHECK` command from CrowPanel
- Partition scheme: `Default 4MB with spiffs` → **Min SPIFFS (1.9MB APP with OTA/190KB SPIFFS)**

**CrowPanel:**

- New `src/core/ota_manager.h/.cpp` — checks manifest, calls `HTTPUpdate`, triggers WROOM OTA after self-update
- New `src/ui/ui_ota.h/.cpp` — LVGL overlay with "Update available" prompt + progress bar
- `ui_settings.cpp` — add "Firmware Update" entry to Settings menu
- `comm_manager.cpp` — handle incoming `OTA_STATUS` from WROOM
- Partition scheme: TBD (see Open Questions above)

**Shared:**

- `firmware_manifest.json` at repo root (served via GitHub raw URL)
- `sync_protocol.h` — add `OTA_STATUS` and `OTA_CHECK` message type constants

### Release Workflow (once implemented)

```
1. Edit firmware, bump FIRMWARE_VERSION in config.h
2. Arduino IDE -> Sketch -> Export Compiled Binary
3. Create a GitHub Release tagged "v1.x.x"
4. Upload wroom_v1.x.x.bin and crowpanel_v1.x.x.bin as release assets
5. Edit firmware_manifest.json with the new version + URLs
6. Commit and push
   -> Devices pick it up within 6 hours (or immediately on next boot)
```

---

## 20. Design Notes

**Partition schemes differ intentionally.** The CrowPanel uses _Huge APP (3MB)_ because LVGL + LovyanGFX + compiled icon assets consume significantly more flash than a typical sketch. OTA is not used on that board yet. The WROOM uses the standard _Default 4MB with spiffs_ scheme.

**PSRAM is enabled only on the CrowPanel.** LVGL's double display buffers (~160 KB each) are allocated from PSRAM at boot. The WROOM-32 module does not have PSRAM populated.

**ESP-NOW channel management.** Both boards must be on the same WiFi channel for ESP-NOW to work. The WROOM monitors the channel in real time and sends `CHANNEL_HOP` notifications to the CrowPanel whenever the AP channel changes, so they stay in sync without a reboot.

**Time source priority.** The WROOM currently uses two clock sources: NTP (requires WiFi, synced on boot) and a `millis()`-based offset as a last resort when offline. A DS3231 hardware RTC is planned as a battery-backed middle tier for future implementation — GPIO21/22 are already reserved for it.

**Employee data lives on the CrowPanel.** The CrowPanel stores the employee list in LittleFS and syncs it from the backend. The WROOM only stores fingerprint template slot-to-employee-ID mappings in its own flash via the `employee_db` module. A sync operation pushes the mapping table from CrowPanel to WROOM over ESP-NOW using a binary framed protocol (`sync_protocol.h`).

**Admin PIN is plaintext.** The PIN is stored as a plain string in `/config.json`. Hashing (e.g. SHA-256 via `mbedtls`) should be added before production deployment.

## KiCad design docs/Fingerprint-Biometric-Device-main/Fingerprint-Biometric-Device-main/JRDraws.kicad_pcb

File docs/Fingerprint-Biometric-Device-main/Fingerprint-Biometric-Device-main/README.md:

Manpro — Biometric Fingerprint Attendance/Access Device

KiCad hardware project for Manpro, a fingerprint-based attendance/access control device. The design is split into two boards — a project (logic) board and a power board — connected via JST connectors carrying GND / +5V / +3.3V.

Project Files
File	Purpose
JRDraws.kicad_pro	KiCad project file
JRDraws.kicad_sch	Main schematic (project board + power board)
JRDraws.kicad_pcb	PCB layout
JRDraws.kicad_prl	Local project settings
Dpad-button-controller.kicad_sch	Sub-schematic for the 5-button D-pad nav controller
fp-lib-table	Footprint library table
Hardware Overview

Main controller (project board)

ESP32 DevKit (38-pin) — main MCU
AS608 fingerprint sensor — RX → G26, TX → G27, T-OUT → G34
DFPlayer Mini (MH2024K) audio module — on G16/G17 via a 5V↔3.3V logic level converter
DS3231 RTC
CrowPanel Node (separate ESP32-S3) touchscreen UI
Buzzer/speaker — on G13
5 navigation push buttons (D-pad sub-board) + a dedicated hardware reset button tied to EN

Power board

USB-C receptacle (power only, 6-pin) input
MCP73871 (QFN-20) LiPo charge/power-path management IC
MT3608 boost converter module
3.7V 5000 mAh LiPo battery
Fuse + protection/flag circuitry

Passives/misc: several resistors and capacitors, 3 LEDs, PWR flag and GND/+5V/+3.3V power symbols throughout.

✔️AS608 TX/RX swap fixed
✔️Decided on a single AS608 sensor (not dual)
✔️ \5 nav buttons + hardware reset button wired correctly
✔️DFPlayer, AS608, and buzzer pins reassigned per updated reference doc

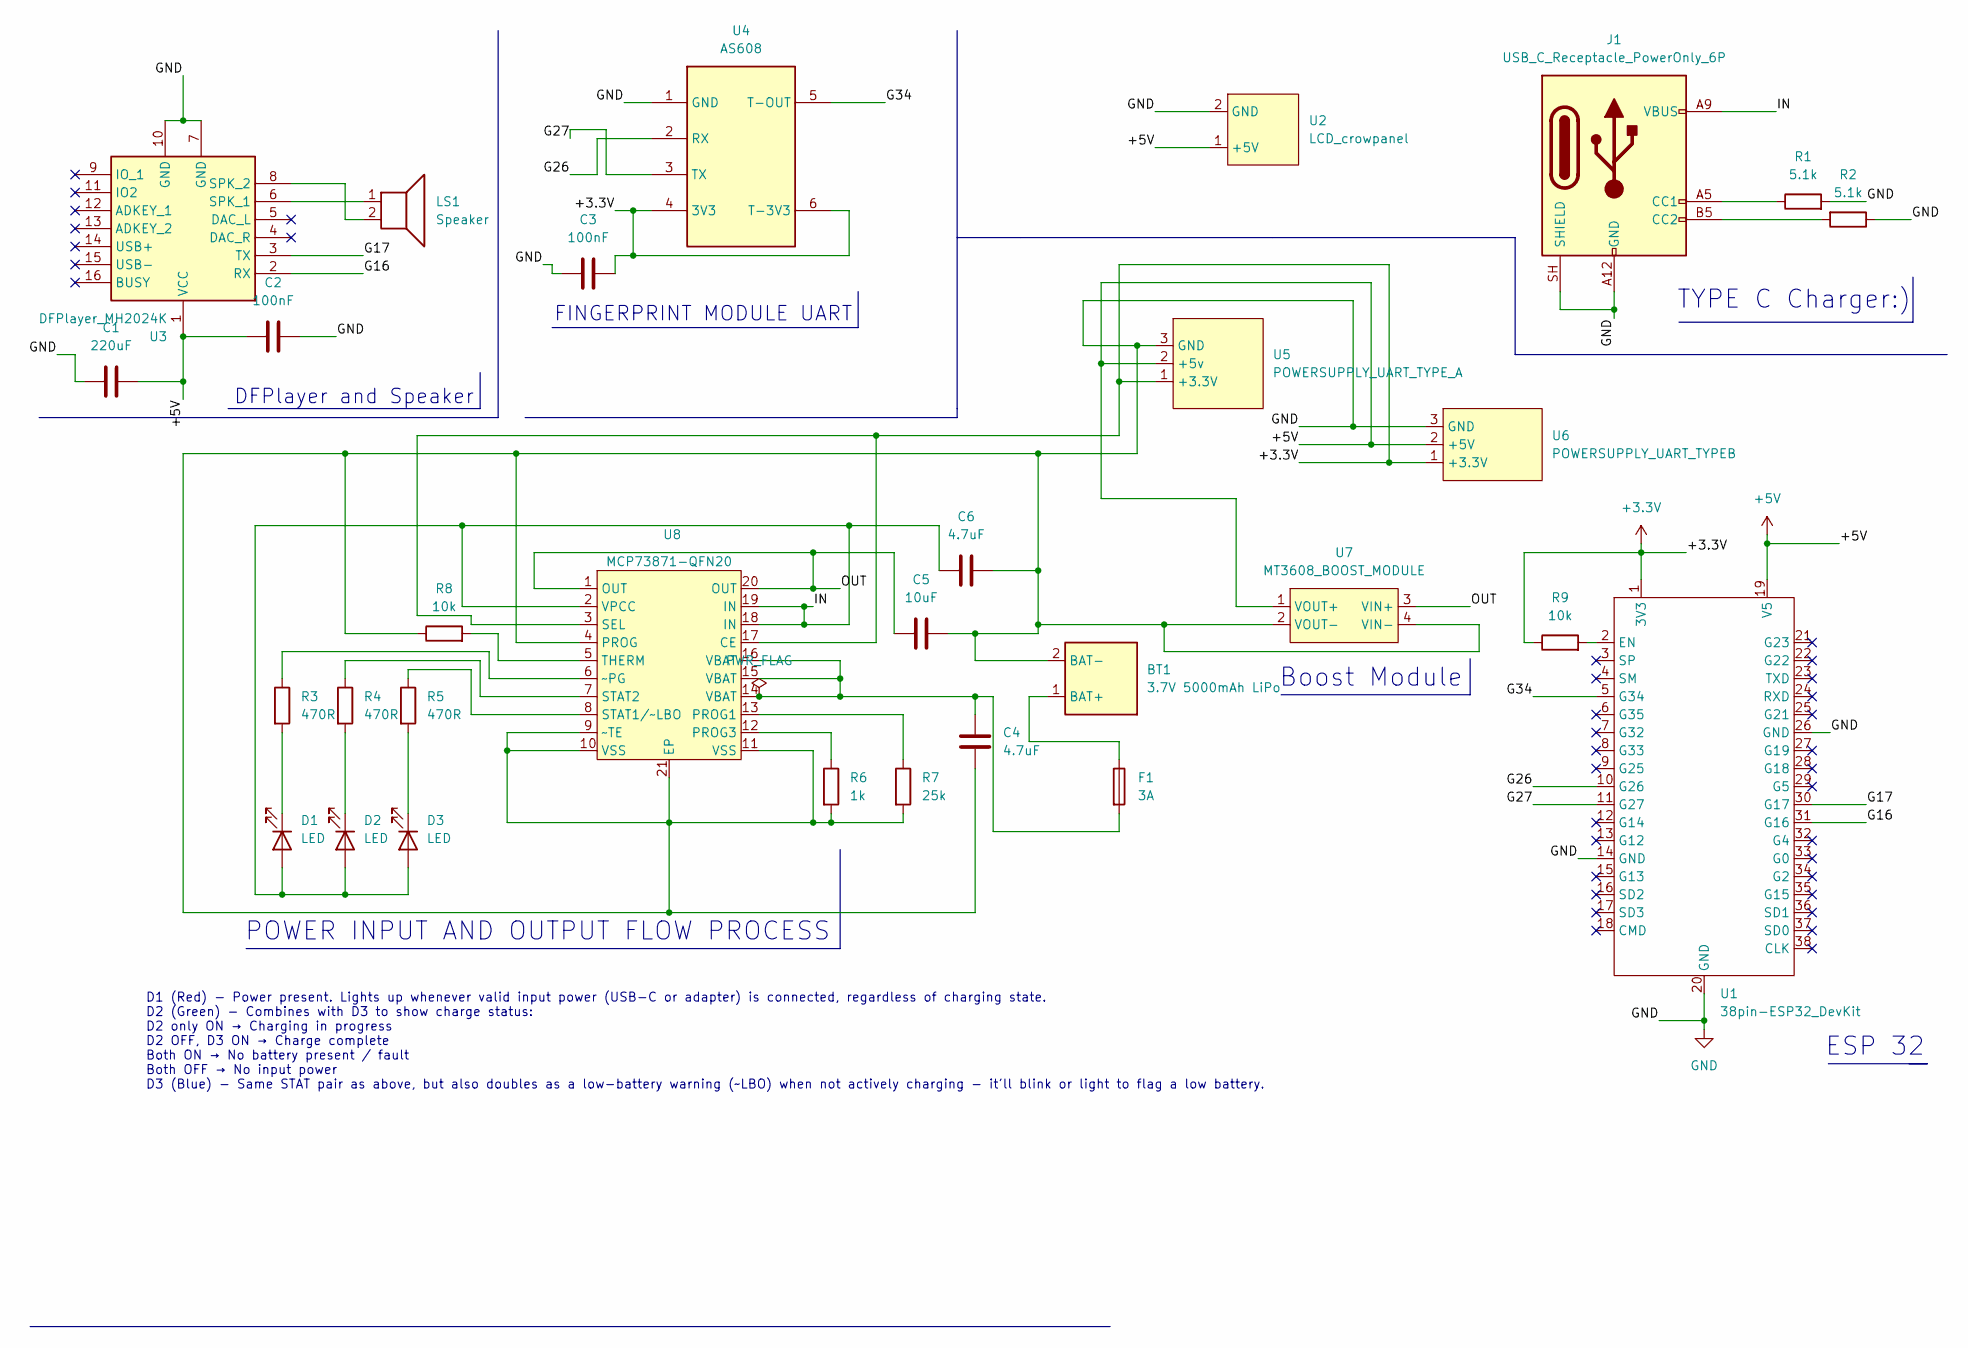
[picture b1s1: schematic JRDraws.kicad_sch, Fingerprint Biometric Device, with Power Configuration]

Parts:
BT1: 3.7V 5000mAh LiPo; JST_PH_S2B-PH-K_1x02_P2.00mm_Horizontal
C1: 220uF; CP_Radial_D8.0mm_P3.50mm
C2, C3: 100nF; C_Disc_D5.0mm_W2.5mm_P5.00mm
C4, C6: 4.7uF; CP_Radial_D5.0mm_P2.00mm
C5: 10uF; CP_Radial_D5.0mm_P2.00mm
D1, D2, D3: LED; LED_D5.0mm
F1: 3A; Fuse_Bourns_MF-RG300
J1: USB_C_Receptacle_PowerOnly_6P; USB_C_Receptacle_GCT_USB4125-xx-x_6P_TopMnt_Horizontal
LS1: Speaker; JST_PH_S2B-PH-K_1x02_P2.00mm_Horizontal
R1, R2: 5.1k; R_Axial_DIN0207_L6.3mm_D2.5mm_P10.16mm_Horizontal
R3, R4, R5: 470R; R_Axial_DIN0207_L6.3mm_D2.5mm_P10.16mm_Horizontal
R6: 1k; R_Axial_DIN0207_L6.3mm_D2.5mm_P10.16mm_Horizontal
R7: 25k; R_Axial_DIN0207_L6.3mm_D2.5mm_P10.16mm_Horizontal
R8, R9: 10k; R_Axial_DIN0207_L6.3mm_D2.5mm_P10.16mm_Horizontal
U1: 38pin-ESP32_DevKit; ESP32
U2: LCD_crowpanel; JST_PH_S2B-PH-K_1x02_P2.00mm_Horizontal
U3: DFPlayer_MH2024K; DFPPLAYER
U4: AS608; JST_PH_S6B-PH-K_1x06_P2.00mm_Horizontal
U5: POWERSUPPLY_UART_TYPE_A; JST_XH_S3B-XH-A_1x03_P2.50mm_Horizontal
U6: POWERSUPPLY_UART_TYPEB; JST_XH_S3B-XH-A_1x03_P2.50mm_Horizontal
U7: MT3608_BOOST_MODULE
U8: MCP73871-QFN20; QFN-20-1EP_4x4mm_P0.5mm_EP2.6x2.6mm

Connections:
+3.3V: C3.2, R9.1, U1.1 (3V3), U4.4 (3V3), U4.6 (T-3V3), U5.1 (+3.3V), U6.1 (+3.3V), U8.3 (SEL), U8.17 (CE)
+5V: C1.1, C2.1, U1.19 (V5), U2.1 (+5V), U3.1 (VCC), U5.2 (+5v), U6.2 (+5V), U7.1 (VOUT+)
/G16: U1.31 (G16), U3.2 (RX)
/G17: U1.30 (G17), U3.3 (TX)
/G26: U1.10 (G26), U4.2 (RX)
/G27: U1.11 (G27), U4.3 (TX)
/G34: U1.5 (G34), U4.5 (T-OUT)
/IN: C6.2, D1.2 (A), D2.2 (A), D3.2 (A), J1.A9 (VBUS), J1.B9 (VBUS), U8.2 (VPCC), U8.18 (IN), U8.19 (IN)
/OUT: C5.2, U7.3 (VIN+), U8.1 (OUT), U8.20 (OUT)
GND: BT1.2 (BAT-), C1.2, C2.2, C3.1, C4.2, C5.1, C6.1, J1.A12 (GND), J1.B12 (GND), J1.SH (SHIELD), R1.2, R2.1, R6.2, R7.2, R8.1, U1.14 (GND), U1.20 (GND), U1.26 (GND), U2.2 (GND), U3.7 (GND), U3.10 (GND), U4.1 (GND), U5.3 (GND), U6.3 (GND), U7.2 (VOUT-), U7.4 (VIN-), U8.4 (PROG), U8.9 (~TE), U8.10 (VSS), U8.11 (VSS), U8.21 (EP)
unnamed: BT1.1 (BAT+), F1.1
unnamed: C4.1, F1.2, U8.14 (VBAT), U8.15 (VBAT), U8.16 (VBAT)
unnamed: D1.1 (K), R3.2
unnamed: D2.1 (K), R4.2
unnamed: D3.1 (K), R5.2
unnamed: J1.A5 (CC1), R1.1
unnamed: J1.B5 (CC2), R2.2
unnamed: R9.2, U1.2 (EN)
unnamed: LS1.1, U3.6 (SPK_1)
unnamed: LS1.2, U3.8 (SPK_2)
unnamed: R7.1, U8.13 (PROG1)
unnamed: R6.1, U8.12 (PROG3)
unnamed: R5.1, U8.8 (STAT1/~LBO)
unnamed: R4.1, U8.7 (STAT2)
unnamed: R8.2, U8.5 (THERM)
unnamed: R3.1, U8.6 (~PG)

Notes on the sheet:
ESP 32
FINGERPRINT MODULE UART
TYPE C Charger:)
Boost Module
D1 (Red) - Power present. Lights up whenever valid input power (USB-C or adapter) is connected, regardless of charging state. D2 (Green) - Combines with D3 to show charge status: D2 only ON → Charging in progress D2 OFF, D3 ON → Charge complete Both ON → No battery present / fault Both OFF → No inp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
POWER INPUT AND OUTPUT FLOW PROCESS
DFPlayer and Speaker

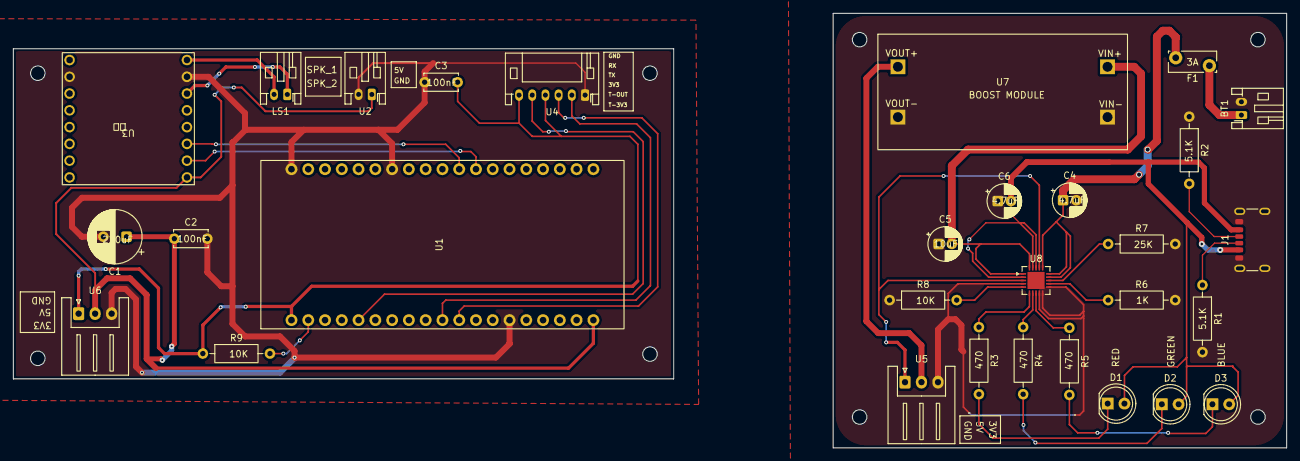
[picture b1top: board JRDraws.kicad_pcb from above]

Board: 2 copper layers, 192.8 x 65.8 mm, 30 parts (0 on the bottom side), 26 nets.
